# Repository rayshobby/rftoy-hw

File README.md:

rftoy-hw
========

Hardware design files for RFtoy

Requires EagleCAD v6.0 or above.

For RFToy Arduino library, visit:
http://github.com/rayshobby/rftoy

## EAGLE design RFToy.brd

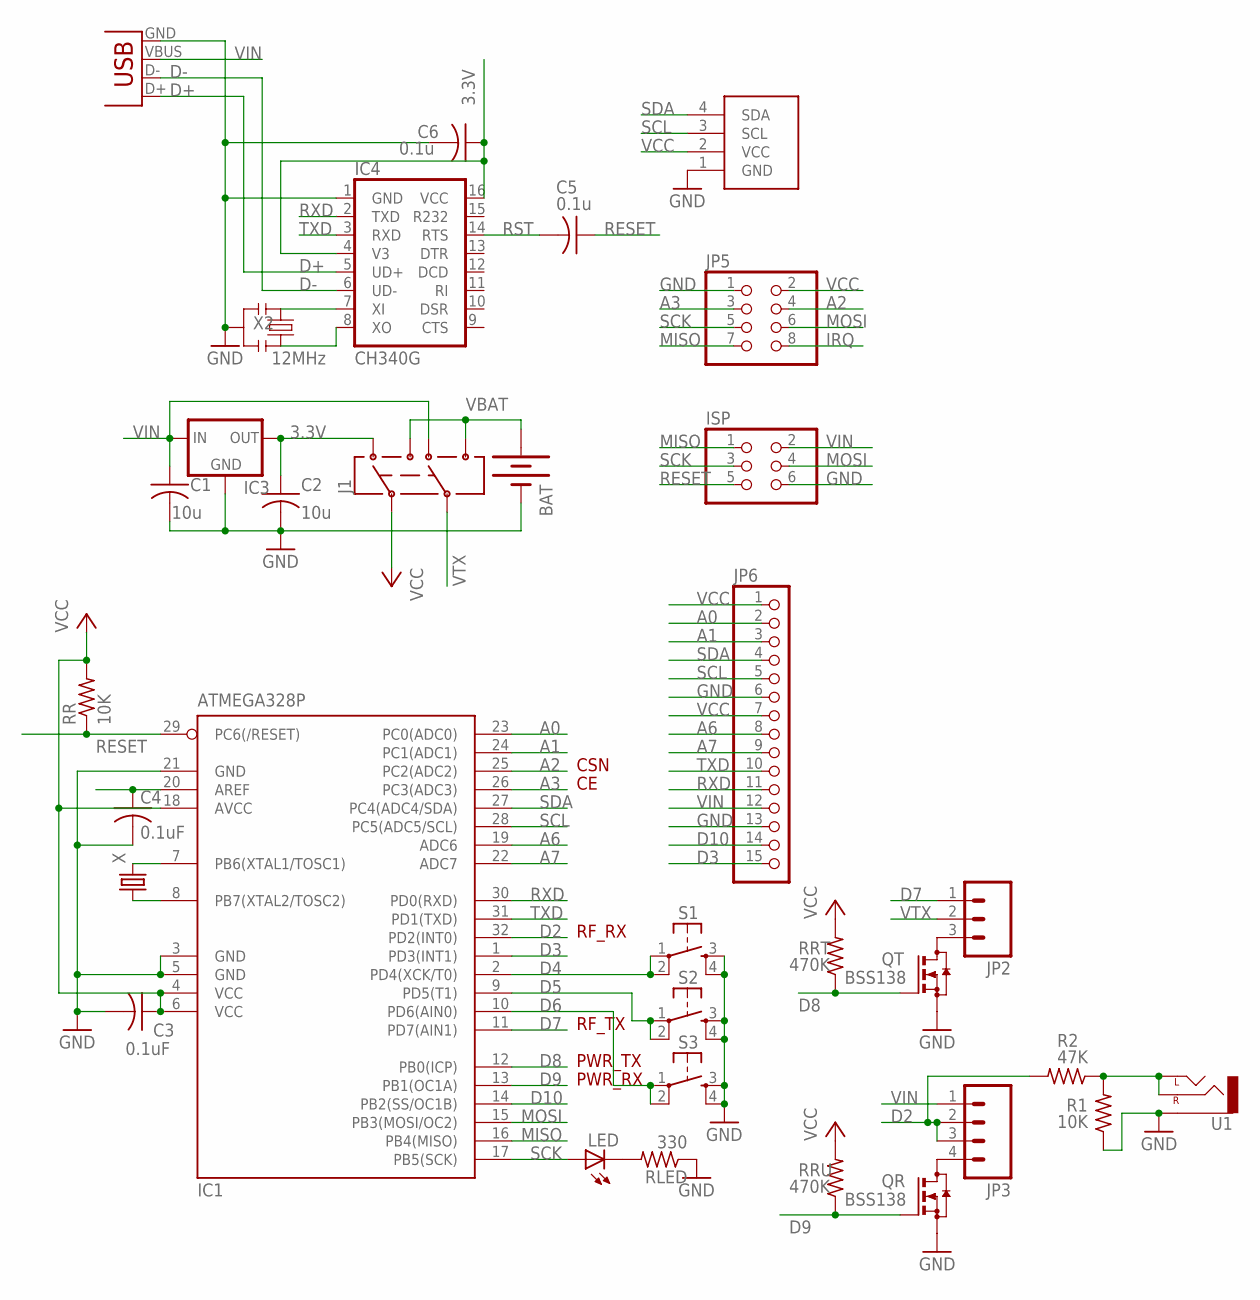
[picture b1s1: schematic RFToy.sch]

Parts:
BAT: BATTERY20PTH; BATTCOM_20MM_PTH
C1, C2: 10u; C0805K
C3, C4: 0.1uF; C0805K
C5, C6: 0.1u; C0805K
IC1: ATMEGA328P; TQFP32-08
IC3: MCP1700SOT233; SOT23
IC4: CH340G; SO16
ISP: PINHD-2X3; 2X03
J1: AYZ0202
JP2: M03LOCK_LONGPADS; 1X03_LOCK_LONGPADS
JP3: M04LOCK; 1X04_LOCK
JP5: PINHD-2X4; 2X04
JP6: PINHD-1X15-CB; 1X15-CB
LED: LEDCHIPLED_0805; CHIPLED_0805
QR: BSS138; SOT23
QT: BSS138; SOT23
R1: 10K; R0805
R2: 47K; R0805
RLED: 330; R0805
RR: 10K; R0805
RRT: 470K; R0805
RRU: 470K; R0805
S1, S2, S3: TAC_SWITCHPTH; TACTILE-PTH
U1: AUDIO-JACKPTH; AUDIO-JACK
U$1: SSD1306_OLED_I2C
X: CRYSTALTC26V; TC26V
X1: USBSMD; USB-MINIB
X2: 12MHz; RESONATOR-SMD

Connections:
3.3V: C2.1, C6.1, IC3.2 (OUT), IC4.4 (V3), IC4.16 (VCC), J1.3 (1)
A0: IC1.23 (PC0(ADC0)), JP6.2
A1: IC1.24 (PC1(ADC1)), JP6.3
A2: IC1.25 (PC2(ADC2)), JP5.4
A3: IC1.26 (PC3(ADC3)), JP5.3
A6: IC1.19 (ADC6), JP6.8
A7: IC1.22 (ADC7), JP6.9
AREF: C4.1, IC1.20 (AREF)
D2: IC1.32 (PD2(INT0)), JP3.2, JP3.3, R2.2
D3: IC1.1 (PD3(INT1)), JP6.15
D4: IC1.2 (PD4(XCK/T0)), S1.1, S1.2
D5: IC1.9 (PD5(T1)), S2.1, S2.2
D6: IC1.10 (PD6(AIN0)), S3.1, S3.2
D7: IC1.11 (PD7(AIN1)), JP2.1
D8: IC1.12 (PB0(ICP)), QT.1 (G), RRT.1
D9: IC1.13 (PB1(OC1A)), QR.1 (G), RRU.1
D10: IC1.14 (PB2(SS/OC1B)), JP6.14
D+: IC4.5 (UD+), X1.D+
D-: IC4.6 (UD-), X1.D-
GND: BAT.2 (-), C1.2, C2.2, C3.2, C4.2, C6.2, IC1.3 (GND), IC1.5 (GND), IC1.21 (GND), IC3.1 (GND), IC4.1 (GND), ISP.6, JP5.1, JP6.6, JP6.13, QR.2 (S), QT.2 (S), R1.1, RLED.1, S1.3, S1.4, S2.3, S2.4, S3.3, S3.4, U1.SLEEVE, U$1.1 (GND), X1.GND, X2.2
IRQ: JP5.8
MISO: IC1.16 (PB4(MISO)), ISP.1, JP5.7
MOSI: IC1.15 (PB3(MOSI/OC2)), ISP.4, JP5.6
unnamed: LED.C, RLED.2
unnamed: IC1.7 (PB6(XTAL1/TOSC1)), X.2
unnamed: IC1.8 (PB7(XTAL2/TOSC2)), X.1
unnamed: R1.2, R2.1, U1.RING (RIGHT), U1.TIP (LEFT)
unnamed: JP3.4, QR.3 (D)
unnamed: JP2.3, QT.3 (D)
unnamed: IC4.7 (XI), X2.1
unnamed: IC4.8 (XO), X2.3
RESET: C5.1, IC1.29 (PC6(/RESET)), ISP.5, RR.1
RST: C5.2, IC4.14 (RTS)
RXD: IC1.30 (PD0(RXD)), IC4.2 (TXD), JP6.11
SCK: IC1.17 (PB5(SCK)), ISP.3, JP5.5, LED.A
SCL: IC1.28 (PC5(ADC5/SCL)), JP6.5, U$1.3 (SCL)
SDA: IC1.27 (PC4(ADC4/SDA)), JP6.4, U$1.4 (SDA)
TXD: IC1.31 (PD1(TXD)), IC4.3 (RXD), JP6.10
VBAT: BAT.1 (+), J1.1 (3), J1.4 (6)
VCC: C3.1, IC1.4 (VCC), IC1.6 (VCC), IC1.18 (AVCC), J1.2, JP5.2, JP6.1, JP6.7, RR.2, RRT.2, RRU.2, U$1.2 (VCC)
VIN: C1.1, IC3.3 (IN), ISP.2, J1.6 (4), JP3.1, JP6.12, X1.VBUS
VTX: J1.5, JP2.2

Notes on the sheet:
RF_RX
PWR_RX
PWR_TX
RF_TX
CSN

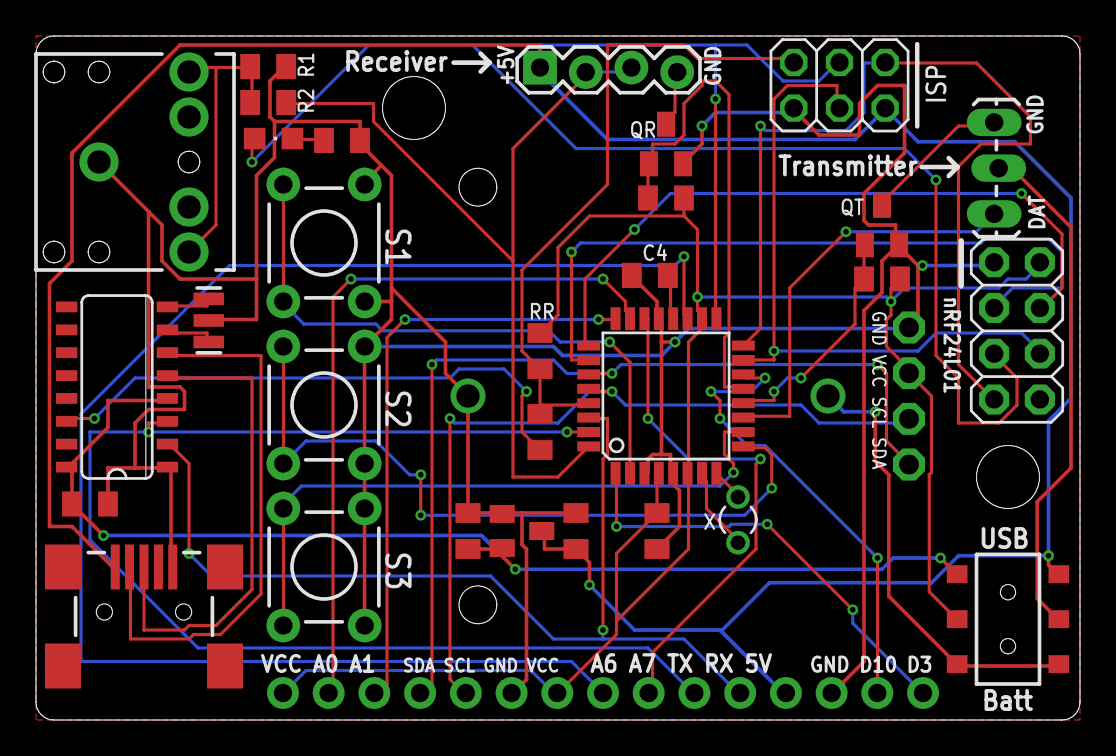
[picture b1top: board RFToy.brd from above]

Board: 2 copper layers, 58.0 x 38.0 mm, 33 parts (1 on the bottom side), 41 nets.

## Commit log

2014-11-09 initial check in of RFToy v1.0 design
2014-11-15 correct pin assignments
